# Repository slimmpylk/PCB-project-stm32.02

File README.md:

# Project Overview

The primary goal of this project was to intricately design the electronics and circuit board for a sophisticated embedded device. By harnessing our team's deep technical expertise, we set out to develop a high-end wireless weather station. This system is powered by the STM32WB microcontroller, renowned for its high performance and reliability in handling wireless communications.

## Implementation Details

Our team is committed to providing a comprehensive solution that not only measures various environmental parameters accurately but also facilitates efficient data transmission through wireless networks. At the heart of our design, the STM32WB microcontroller boasts Bluetooth capabilities, making it an excellent choice for our advanced weather monitoring system.

## Key Features

- **Real-Time Environmental Monitoring:** The station is capable of measuring temperature and humidity.
- **Energy-Efficient Design:** Focuses on low power consumption, ideal for long-term deployment in remote areas with minimal maintenance requirements.

This project is a testament to our team's dedication to pushing the boundaries of innovation and excellence in embedded systems design.

## Pics

# PCB

# PCB-schema

# 3D-pic

# Built PCB

# STM close-up

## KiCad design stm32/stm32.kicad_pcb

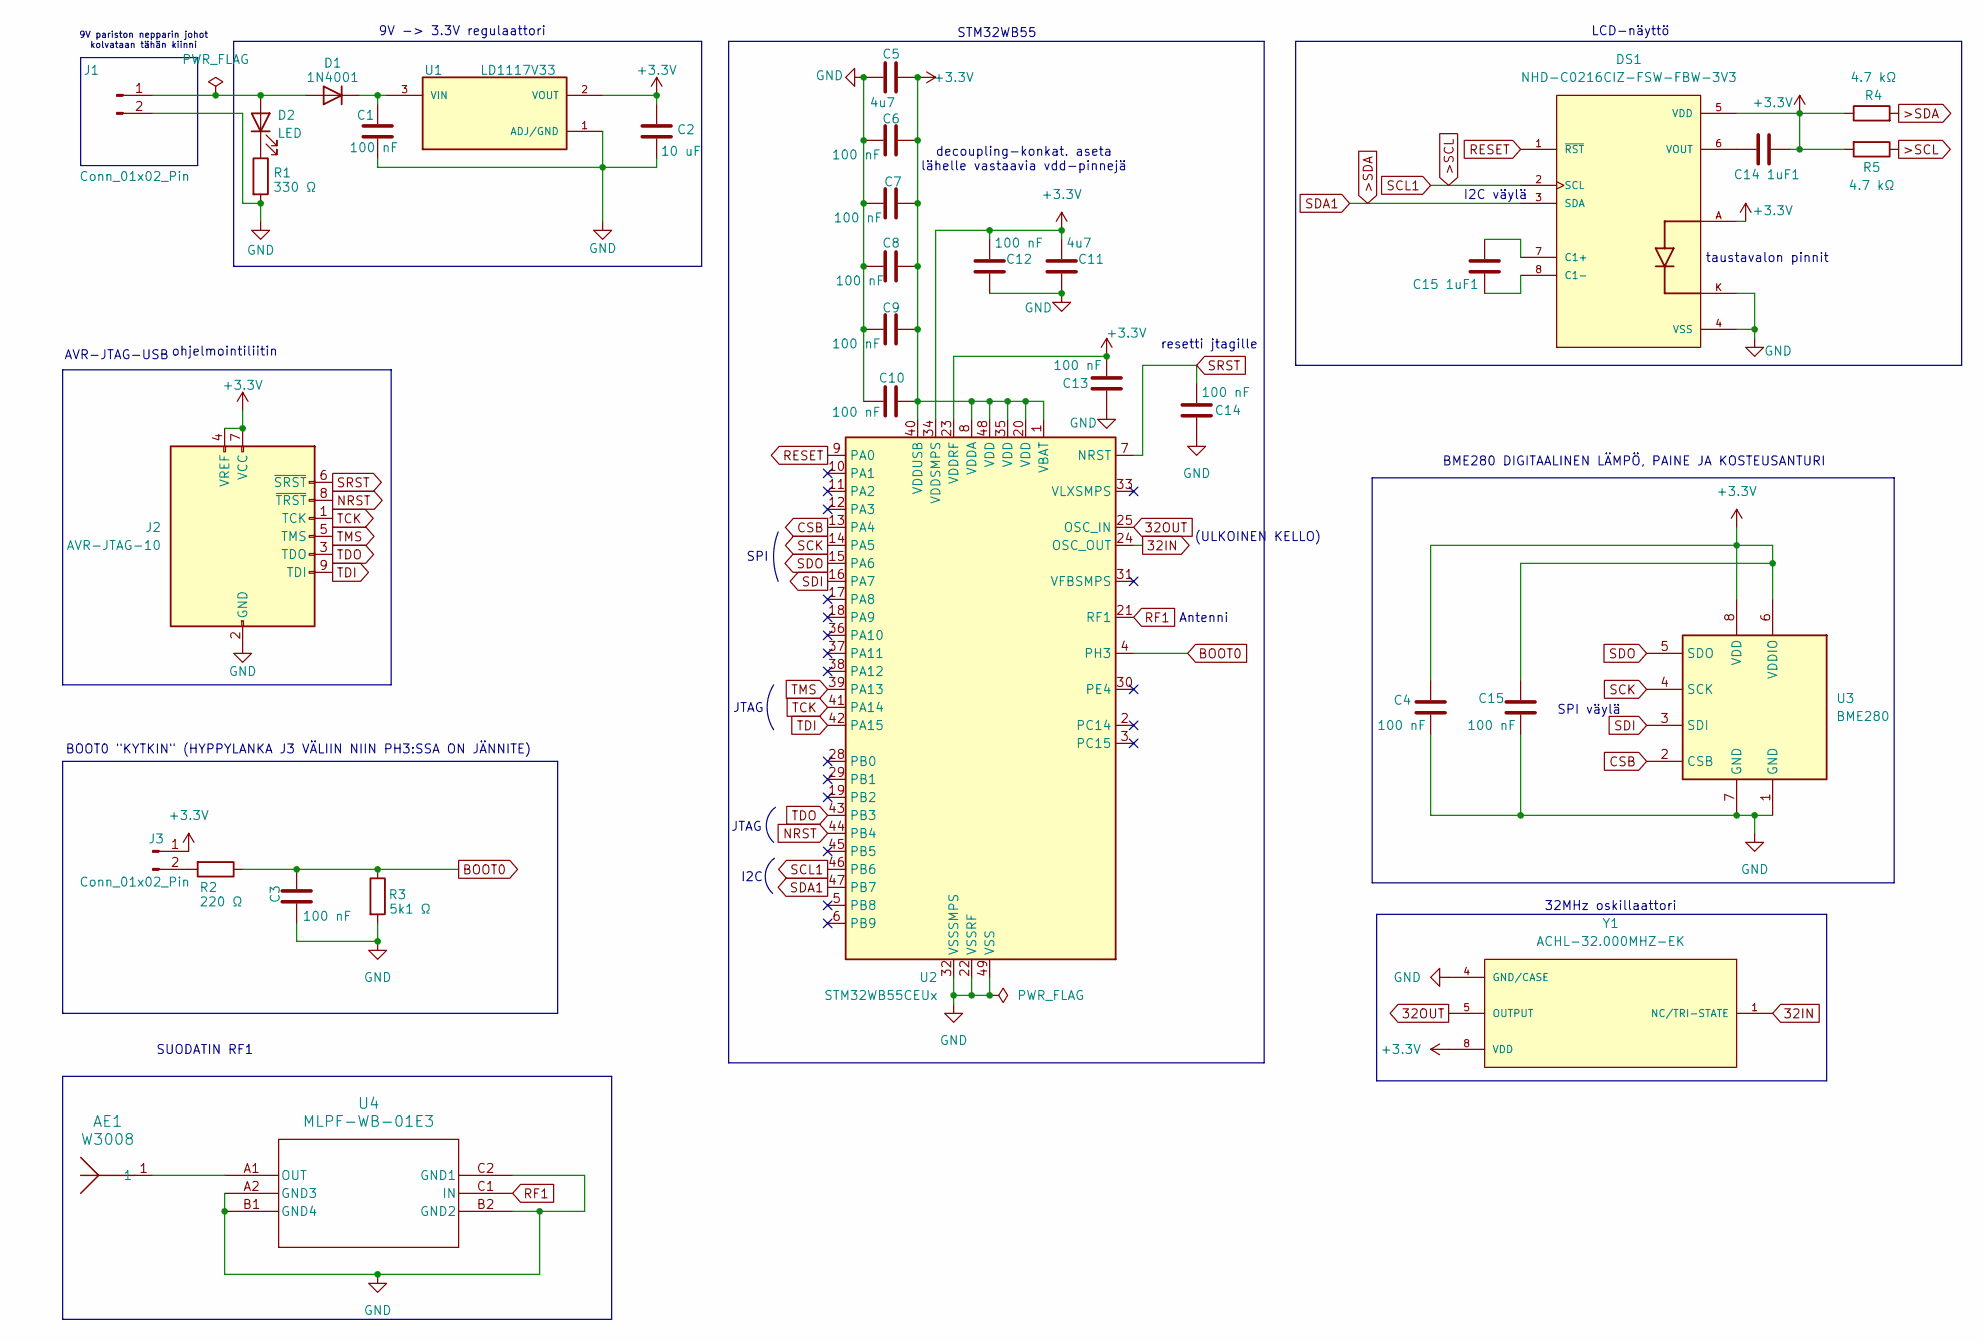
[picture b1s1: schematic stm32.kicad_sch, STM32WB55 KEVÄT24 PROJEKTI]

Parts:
AE1: W3008; ANT_W3008_PUL
C1, C3, C4, C6, C7, C8, C9, C10, C12, C13, C14, C15: 100 nF; C_Disc_D3.0mm_W1.6mm_P2.50mm
C2: 10 uF; C_Disc_D3.0mm_W1.6mm_P2.50mm
C5, C11: 4u7; C_Disc_D3.0mm_W1.6mm_P2.50mm
C14 1uF1: C_Disc_D3.0mm_W1.6mm_P2.50mm
C15 1uF1: 1uF; C_Disc_D3.0mm_W1.6mm_P2.50mm
D1: 1N4001; D_DO-41_SOD81_P10.16mm_Horizontal
D2: LED; LED_D5.0mm_Clear
DS1: NHD-C0216CIZ-FSW-FBW-3V3; LCD_NHD-C0216CIZ-FSW-FBW-3V3; PARTREV 6/4/19
J1, J3: Conn_01x02_Pin; SolderWire-0.1sqmm_1x02_P3.6mm_D0.4mm_OD1mm
J2: AVR-JTAG-10; IDC-Header_2x05_P2.54mm_Vertical
R1: 330 Ω; R_Axial_DIN0204_L3.6mm_D1.6mm_P5.08mm_Horizontal
R2: 220 Ω; R_Axial_DIN0204_L3.6mm_D1.6mm_P5.08mm_Horizontal
R3: 5k1 Ω; R_Axial_DIN0204_L3.6mm_D1.6mm_P5.08mm_Horizontal
R4, R5: 4.7 kΩ; R_Axial_DIN0204_L3.6mm_D1.6mm_P5.08mm_Horizontal
U1: LD1117V33; TO255P1020X450X1968-3; PARTREV 37
U2: STM32WB55CEUx; QFN-48-1EP_7x7mm_P0.5mm_EP5.6x5.6mm
U3: BME280; Bosch_LGA-8_2.5x2.5mm_P0.65mm_ClockwisePinNumbering
U4: MLPF-WB-01E3; CSP6_BUMPLESS_STM
Y1: ACHL-32.000MHZ-EK; XTAL_ACHL-32.000MHZ-EK; PARTREV 01.20.16

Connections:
32IN: U2.24 (OSC_OUT), Y1.1 (NC/TRI-STATE)
32OUT: U2.25 (OSC_IN), Y1.5 (OUTPUT)
+3.3V: C2.1, C4.1, C5.1, C6.1, C7.1, C8.1, C9.1, C10.1, C11.1, C12.1, C13.1, C14 1uF1.1, C15.1, DS1.5 (VDD), DS1.A, J2.4 (VREF), J2.7 (VCC), J3.1, R4.1, R5.2, U1.2 (VOUT), U2.1 (VBAT), U2.8 (VDDA), U2.20 (VDD), U2.23 (VDDRF), U2.34 (VDDSMPS), U2.35 (VDD), U2.40 (VDDUSB), U2.48 (VDD), U3.6 (VDDIO), U3.8 (VDD), Y1.8 (VDD)
>SCL: DS1.2 (SCL), R5.1, U2.46 (PB6)
>SDA: DS1.3 (SDA), R4.2, U2.47 (PB7)
BOOT0: C3.1, R2.1, R3.1, U2.4 (PH3)
CSB: U2.13 (PA4), U3.2 (CSB)
GND: C1.2, C2.2, C3.2, C4.2, C5.2, C6.2, C7.2, C8.2, C9.2, C10.2, C11.2, C12.2, C13.2, C14.2, C15.2, DS1.4 (VSS), DS1.K, J1.2, J2.2 (GND), J2.10 (GND), R1.2, R3.2, U1.1 (ADJ/GND), U2.22 (VSSRF), U2.32 (VSSSMPS), U2.49 (VSS), U3.1 (GND), U3.7 (GND), U4.A2 (GND3), U4.B1 (GND4), U4.B2 (GND2), U4.C2 (GND1), Y1.4 (GND/CASE)
NRST: J2.8 (~TRST), U2.44 (PB4)
unnamed: D1.2 (A), D2.2 (A), J1.1
unnamed: C1.1, D1.1 (K), U1.3 (VIN)
unnamed: D2.1 (K), R1.1
unnamed: C15 1uF1.1, DS1.7 (C1+)
unnamed: C15 1uF1.2, DS1.8 (C1-)
unnamed: C14 1uF1.2, DS1.6 (VOUT)
unnamed: J3.2, R2.2
unnamed: AE1.1, U4.A1 (OUT)
RESET: DS1.1 (~RST), U2.9 (PA0)
RF1: U2.21 (RF1), U4.C1 (IN)
SCK: U2.14 (PA5), U3.4 (SCK)
SDI: U2.16 (PA7), U3.3 (SDI)
SDO: U2.15 (PA6), U3.5 (SDO)
SRST: C14.1, J2.6 (~SRST), U2.7 (NRST)
TCK: J2.1 (TCK), U2.41 (PA14)
TDI: J2.9 (TDI), U2.42 (PA15)
TDO: J2.3 (TDO), U2.43 (PB3)
TMS: J2.5 (TMS), U2.39 (PA13)

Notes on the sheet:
BME280 DIGITAALINEN LÄMPÖ, PAINE JA KOSTEUSANTURI
STM32WB55
Antenni
resetti jtagille
I2C väylä
decoupling-konkat. aseta lähelle vastaavia vdd-pinnejä
9V pariston nepparin johot kolvataan tähän kiinni
BOOT0 "KYTKIN" (HYPPYLANKA J3 VÄLIIN NIIN PH3:SSA ON JÄNNITE)
9V -> 3.3V regulaattori
JTAG
32MHz oskillaattori
AVR-JTAG-USB
I2C
SUODATIN RF1
(ULKOINEN KELLO)
LCD-näyttö
taustavalon pinnit
ohjelmointiliitin
SPI väylä
SPI

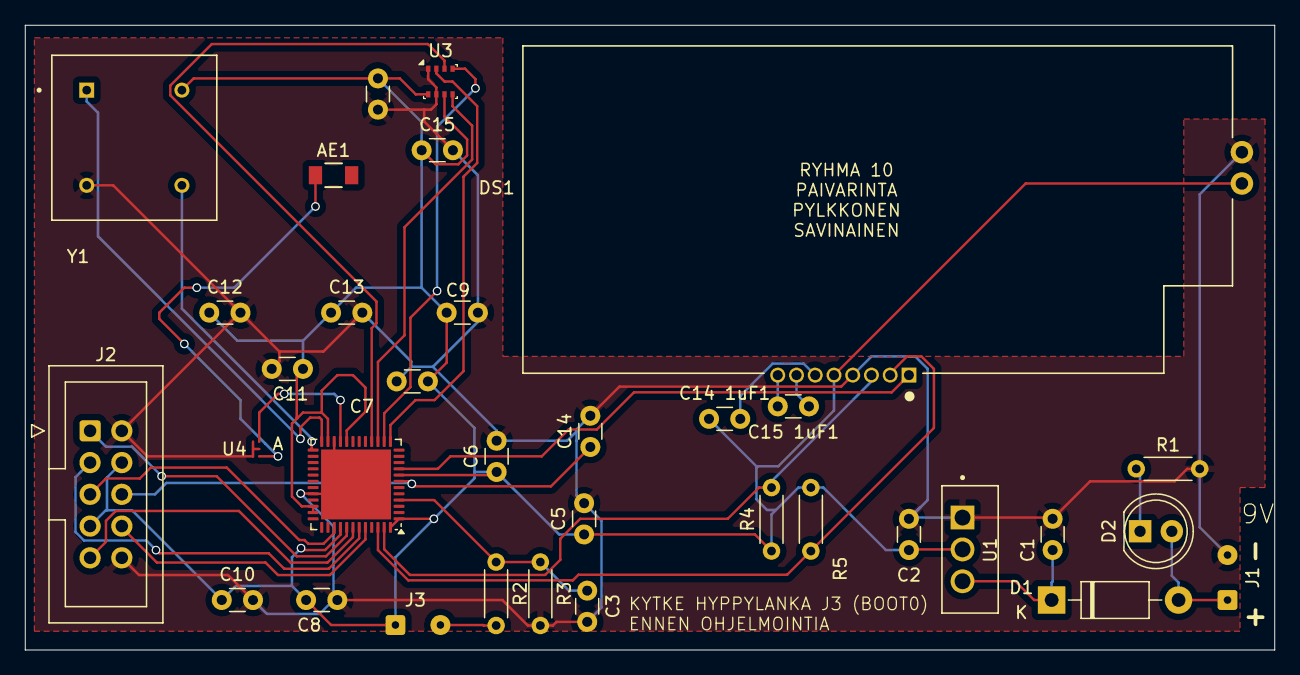
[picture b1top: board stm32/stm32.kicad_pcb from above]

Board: 2 copper layers, 100.0 x 50.0 mm, 34 parts (0 on the bottom side), 27 nets.

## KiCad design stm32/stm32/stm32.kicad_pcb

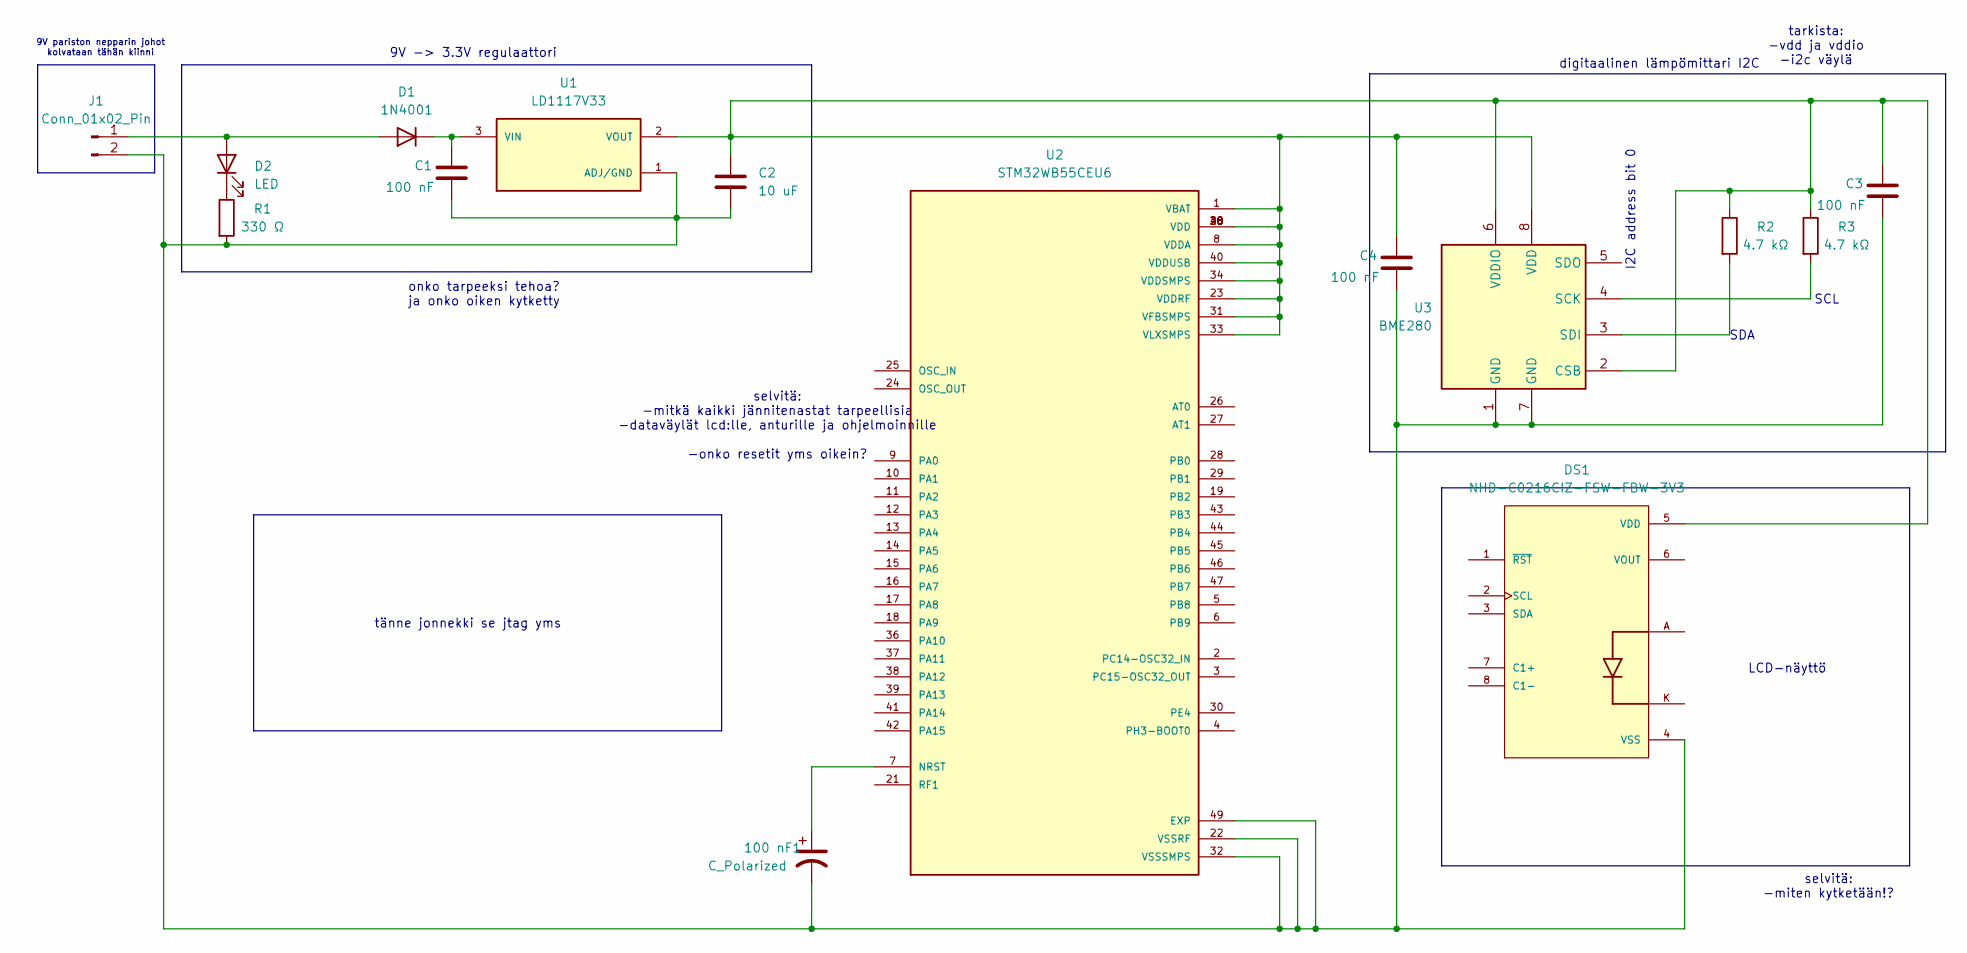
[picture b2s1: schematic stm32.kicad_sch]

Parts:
100 nF1: C_Polarized; CP_Elec_3x5.3
C1, C3, C4: 100 nF; C_Elec_3x5.4
C2: 10 uF; C_Elec_3x5.4
D1: 1N4001; D_DO-41_SOD81_P10.16mm_Horizontal
D2: LED; LED_D5.0mm_Clear
DS1: NHD-C0216CIZ-FSW-FBW-3V3; LCD_NHD-C0216CIZ-FSW-FBW-3V3; PARTREV 6/4/19
J1: Conn_01x02_Pin; SolderWire-0.1sqmm_1x02_P3.6mm_D0.4mm_OD1mm
R1: 330 Ω; R_Axial_DIN0204_L3.6mm_D1.6mm_P5.08mm_Horizontal
R2, R3: 4.7 kΩ; R_Axial_DIN0204_L3.6mm_D1.6mm_P5.08mm_Horizontal
U1: LD1117V33; TO255P1020X450X1968-3; PARTREV 37
U2: STM32WB55CEU6; QFN50P700X700X60-49N; PARTREV 5
U3: BME280; Bosch_LGA-8_2.5x2.5mm_P0.65mm_ClockwisePinNumbering

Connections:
unnamed: D1.2 (A), D2.2 (A), J1.1
unnamed: C1.1, D1.1 (K), U1.3 (VIN)
unnamed: D2.1 (K), R1.1
unnamed: C2.1, C3.1, C4.1, DS1.5 (VDD), R2.1, R3.1, U1.2 (VOUT), U2.1 (VBAT), U2.8 (VDDA), U2.20 (VDD), U2.23 (VDDRF), U2.31 (VFBSMPS), U2.33 (VLXSMPS), U2.34 (VDDSMPS), U2.35 (VDD), U2.40 (VDDUSB), U2.48 (VDD), U3.2 (CSB), U3.6 (VDDIO), U3.8 (VDD)
unnamed: 100 nF1.2, C1.2, C2.2, C3.2, C4.2, DS1.4 (VSS), J1.2, R1.2, U1.1 (ADJ/GND), U2.22 (VSSRF), U2.32 (VSSSMPS), U2.49 (EXP), U3.1 (GND), U3.7 (GND)
unnamed: 100 nF1.1, U2.7 (NRST)
unnamed: R3.2, U3.4 (SCK)
unnamed: R2.2, U3.3 (SDI)

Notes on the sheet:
SDA
tarkista: -vdd ja vddio -i2c väylä
selvitä: -mitkä kaikki jännitenastat tarpeellisia -dataväylät lcd:lle, anturille ja ohjelmoinnille -onko resetit yms oikein?
onko tarpeeksi tehoa? ja onko oiken kytketty
selvitä: -miten kytketään!?
I2C address bit 0
9V pariston nepparin johot kolvataan tähän kiinni
SCL
tänne jonnekki se jtag yms
LCD-näyttö
digitaalinen lämpömittari I2C
9V -> 3.3V regulaattori

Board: 2 copper layers, 15 parts (0 on the bottom side), 8 nets, no tracks yet.
